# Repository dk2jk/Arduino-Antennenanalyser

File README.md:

<b>Arduino Antennenanalyser</b>

Dieser Antennenanalyser basiert auf Ver&ouml;ffendlichungen von K6BEZ und DG7EAO.

Der Antennenanalyser besteht aus einer Ohmschen SWR Messbr&uuml;cke('Resistive SWR Bridge'), die von einem DDS- Generator gespeist wird.

Die Einstellung der Frequenz und die Messung der Br&uuml;ckenspannung erfolgt &uuml;ber einen Arduino - Mikrocontroller.
Ein PC dient zur Anzeige und Bedienung.

<a href="https://github.com/dk2jk/arduino_antennenanalyser/tree/master/documents">->Beschreibung</a>

Bedienprogramm VNA.exe:
siehe: Abschnitt:&nbsp; "VNA PC Software"  in: <a href="http://www.dg7eao.de/arduino/antennen-analysator/">http://www.dg7eao.de/arduino/antennen-analysator/</a>

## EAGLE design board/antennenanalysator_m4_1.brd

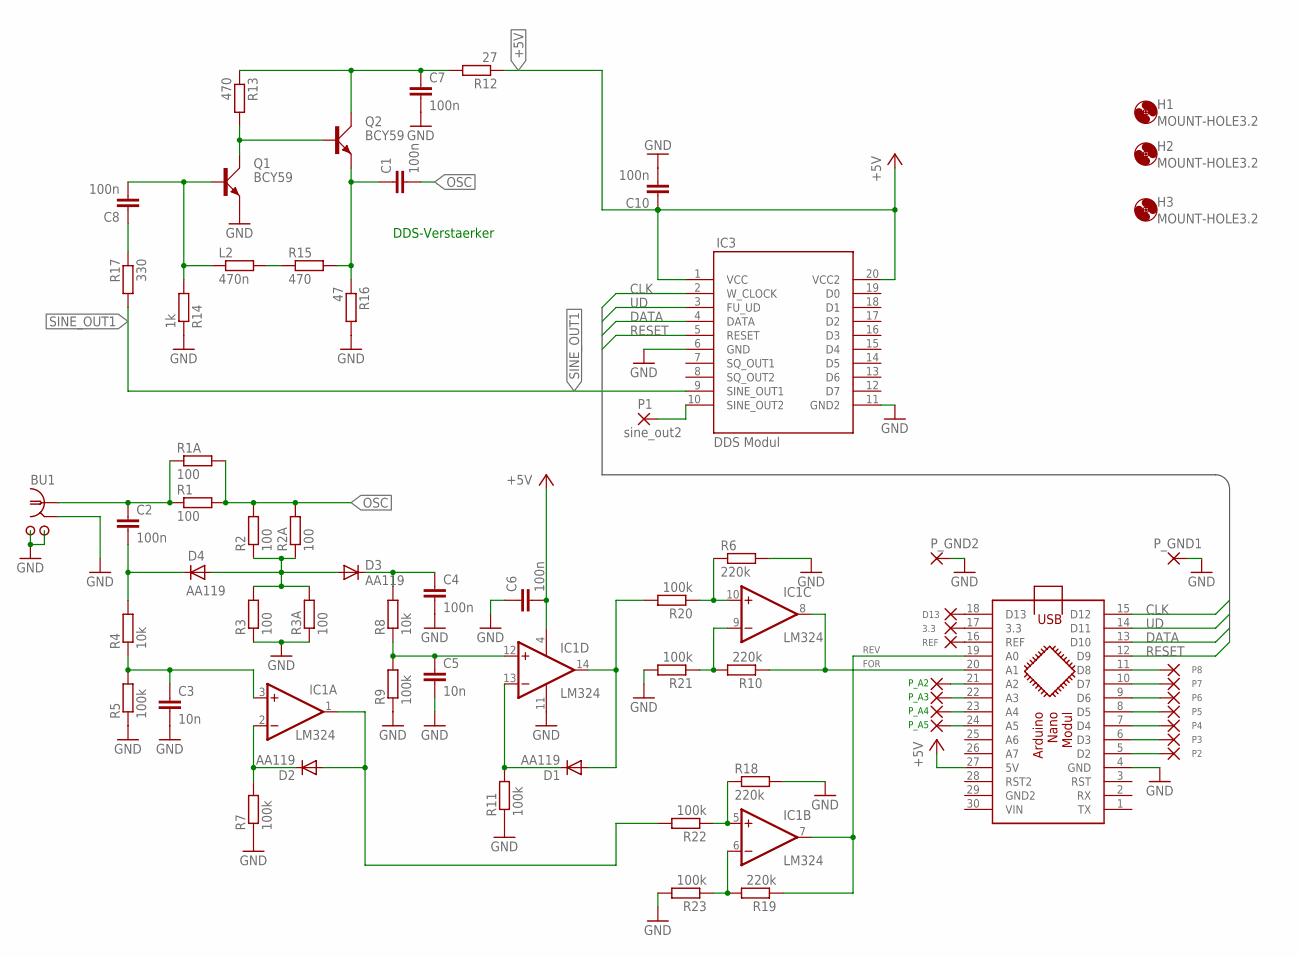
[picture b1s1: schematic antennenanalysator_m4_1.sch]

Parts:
3.3: 1,6/0,8
ARDIUNO_NANO: ARDUINO_NANO
BU1: BNC_1BNC_L; BNC
C1, C2, C4, C6, C7, C8, C10: 100n; C025-025X050
C3, C5: 10n; C025-025X050
D1, D2, D3, D4: AA119; DO07
D13: 1,6/0,8
H1, H2, H3: MOUNT-HOLE3.2; 3,2
IC1: LM324; DIL14
IC3: DDS Modul; MODULE
L2: 470n; 0207/10
P1: sine_out2; 1,6/0,8
P2, P3, P4, P5, P6, P7, P8: 1,6/0,8
P_A2: 1,6/0,8
P_A3, P_A4, P_A5: 1,6/0,8
P_GND1, P_GND2: 1,6/0,8
Q1, Q2: BCY59; TO18A
R1, R1A, R2, R2A, R3, R3A: 100; 0207/10
R4, R8: 10k; 0207/10
R5, R7, R9, R11, R20, R21, R22, R23: 100k; 0207/10
R6, R10, R18, R19: 220k; 0207/10
R12: 27; 0207/10
R13, R15: 470; 0207/10
R14: 1k; 0207/10
R16: 47; 0207/10
R17: 330; 0207/10
REF: 1,6/0,8

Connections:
+5V: ARDIUNO_NANO.27 (5V), C6.2, C10.1, IC1.4 (V+), IC3.1 (VCC), IC3.20 (VCC2), R12.1
ANT: BU1.SIGNAL (SEELE), C2.1, R1.1, R1A.1
CLK: ARDIUNO_NANO.15 (D12), IC3.2 (W_CLOCK)
D3_K: C4.1, D3.C, R8.2
D4_K: C2.2, D4.C, R4.2
DATA: ARDIUNO_NANO.13 (D10), IC3.4 (DATA)
FOR: ARDIUNO_NANO.20 (A1), IC1.8 (OUT), R10.1
GND: ARDIUNO_NANO.4 (GND), BU1.GND, BU1.M1, BU1.M2, C3.2, C4.2, C5.2, C6.1, C7.2, C10.2, IC1.11 (V-), IC3.6 (GND), IC3.11 (GND2), P_GND1.1, P_GND2.1, Q1.E, R3.1, R3A.1, R5.1, R6.2, R7.1, R9.1, R11.1, R14.1, R16.2, R18.2, R21.2, R23.2
unnamed: C3.1, IC1.3 (+IN), R4.1, R5.2
unnamed: ARDIUNO_NANO.16 (REF), REF.1
unnamed: D3.A, D4.A, R2.1, R2A.1, R3.2, R3A.2
unnamed: D2.C, IC1.2 (-IN), R7.2
unnamed: 3.3.1, ARDIUNO_NANO.17 (3.3)
unnamed: ARDIUNO_NANO.18 (D13), D13.1
unnamed: C5.1, IC1.12 (+IN), R8.1, R9.2
unnamed: D1.C, IC1.13 (-IN), R11.2
unnamed: C7.1, Q2.C, R12.2, R13.1
unnamed: C8.1, R17.1
unnamed: L2.2, R15.1
unnamed: Q1.C, Q2.B, R13.2
unnamed: C1.1, Q2.E, R15.2, R16.1
unnamed: C8.2, L2.1, Q1.B, R14.2
unnamed: IC3.10 (SINE_OUT2), P1.1
unnamed: ARDIUNO_NANO.11 (D8), P8.1
unnamed: ARDIUNO_NANO.10 (D7), P7.1
unnamed: ARDIUNO_NANO.9 (D6), P6.1
unnamed: ARDIUNO_NANO.8 (D5), P5.1
unnamed: ARDIUNO_NANO.7 (D4), P4.1
unnamed: ARDIUNO_NANO.6 (D3), P3.1
unnamed: ARDIUNO_NANO.5 (D2), P2.1
unnamed: ARDIUNO_NANO.21 (A2), P_A2.1
unnamed: D1.A, IC1.14 (OUT), R20.2
unnamed: IC1.9 (-IN), R10.2, R21.1
unnamed: D2.A, IC1.1 (OUT), R22.2
unnamed: IC1.6 (-IN), R19.2, R23.1
unnamed: ARDIUNO_NANO.22 (A3), P_A3.1
unnamed: ARDIUNO_NANO.23 (A4), P_A4.1
unnamed: IC1.5 (+IN), R18.1, R22.1
unnamed: IC1.10 (+IN), R6.1, R20.1
unnamed: ARDIUNO_NANO.24 (A5), P_A5.1
OSC: C1.2, R1.2, R1A.2, R2.2, R2A.2
RESET: ARDIUNO_NANO.12 (D9), IC3.5 (RESET)
REV: ARDIUNO_NANO.19 (A0), IC1.7 (OUT), R19.1
SINE_OUT1: IC3.9 (SINE_OUT1), R17.2
UD: ARDIUNO_NANO.14 (D11), IC3.3 (FU_UD)

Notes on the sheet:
DDS-Verstaerker

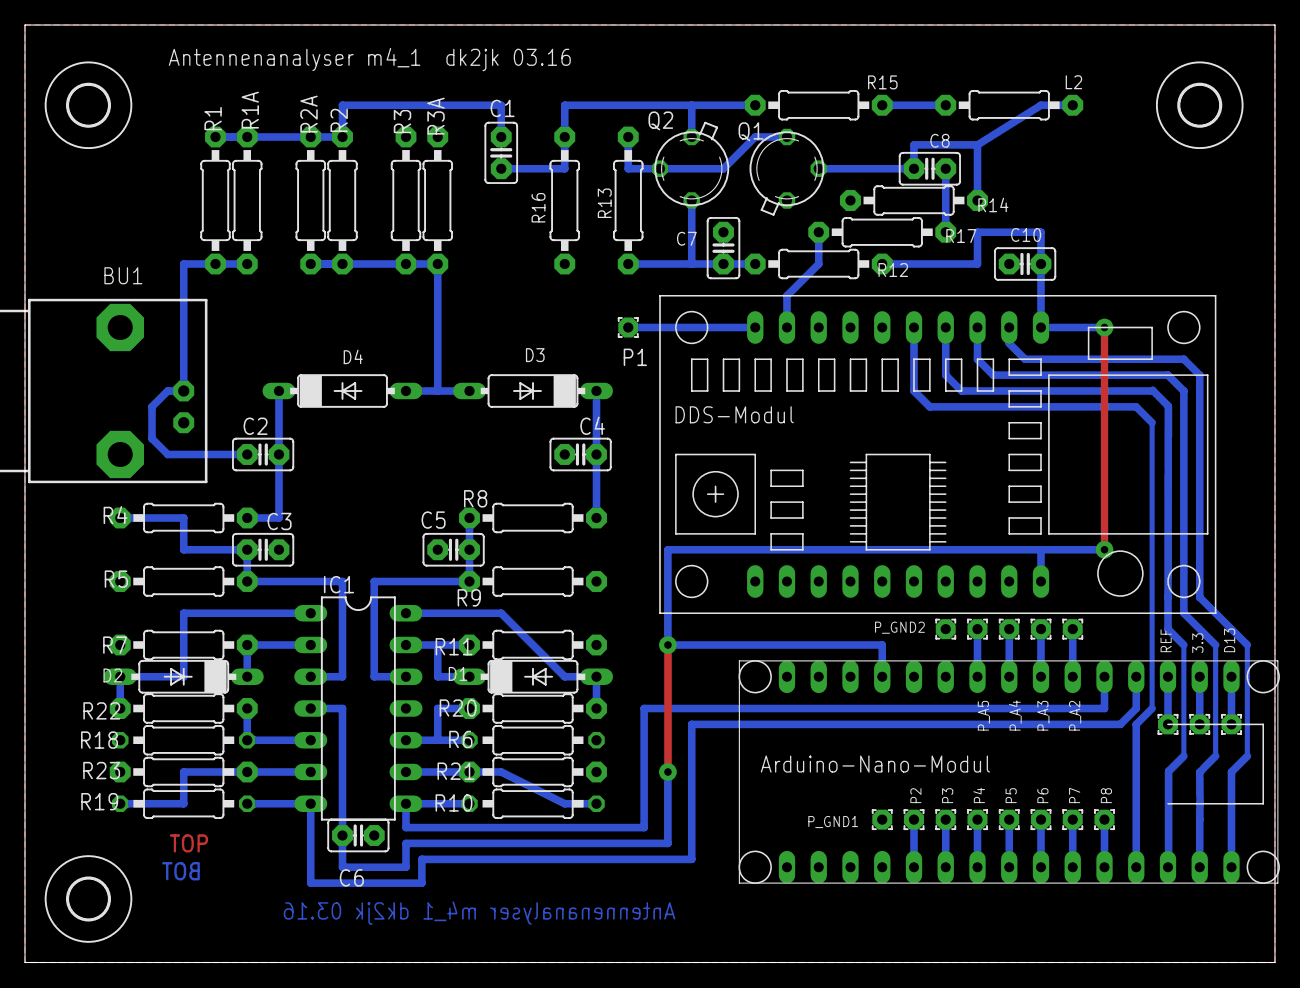
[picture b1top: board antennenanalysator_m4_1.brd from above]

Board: 2 copper layers, 100.0 x 75.0 mm, 66 parts (0 on the bottom side), 45 nets.

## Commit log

2019-05-21 Create xx
2019-05-21 Create board
2019-05-21 Create documents.txt
    dummy
2019-05-21 Create dds_sweeper2_2
